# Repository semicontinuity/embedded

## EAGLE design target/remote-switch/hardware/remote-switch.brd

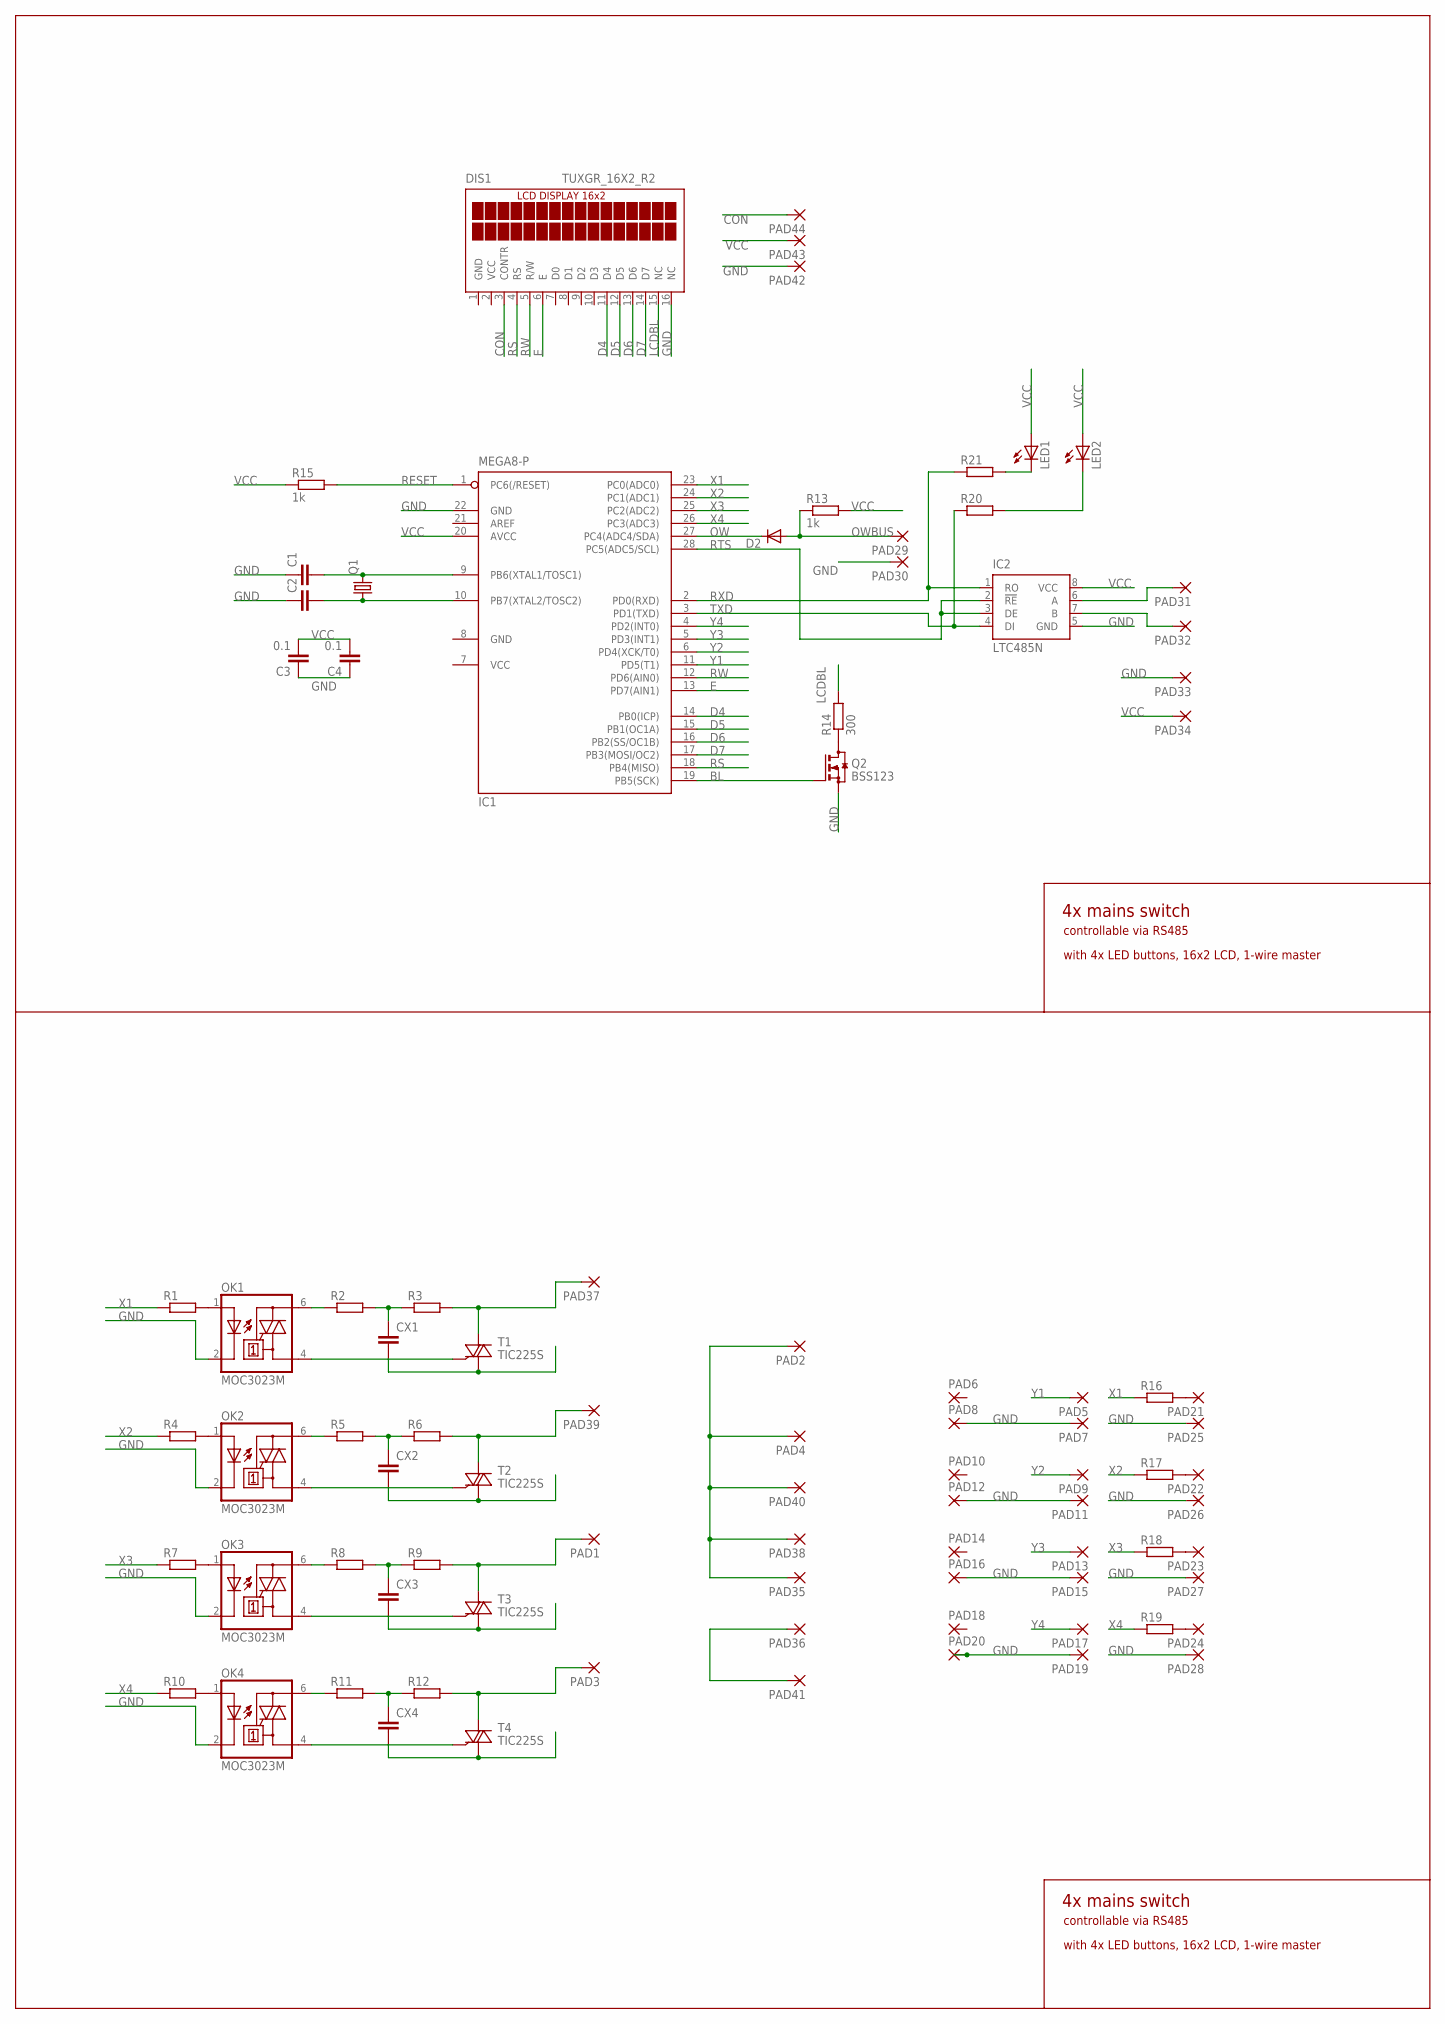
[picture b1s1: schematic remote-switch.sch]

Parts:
C1, C2: C-EUC0805; C0805
C3, C4: 0.1; C0805
CX1, CX2, CX3, CX4: CXXC15B5; XC15B5
D2: DIODE-MINIMELF; MINIMELF
DIS1: TUXGR_16X2_R2
IC1: MEGA8-P; DIL28-3
IC2: LTC485N; DIL08
LED1, LED2: LEDSML0805; SML0805
OK1, OK2, OK3, OK4: MOC3023M; DIL06
PAD1, PAD2, PAD3, PAD4, PAD29, PAD30, PAD31, PAD32, PAD33, PAD34, PAD35, PAD36, PAD37, PAD38, PAD39, PAD40, PAD41: 2,54/0,8
PAD5, PAD6, PAD7, PAD8, PAD9, PAD10, PAD11, PAD12, PAD13, PAD14, PAD15, PAD16, PAD17, PAD18, PAD19, PAD20, PAD21, PAD22, PAD23, PAD24, PAD25, PAD26, PAD27, PAD28, PAD42, PAD43, PAD44: 1,6/0,8
Q1: CRYSTALHC49S; HC49/S
Q2: BSS123; SOT23
R1, R4, R7, R10, R16, R17, R18, R19, R20, R21: R-EU_M0805; M0805
R2, R3, R5, R6, R8, R9, R11, R12: R-EU_R1206; R1206
R13, R15: 1k; R0805
R14: 300; R0805
T1, T2, T3, T4: TIC225S; TO220DS

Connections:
BL: IC1.19 (PB5(SCK)), Q2.1 (G)
CON: DIS1.3 (CONTR), PAD44.1
D4: DIS1.11 (D4), IC1.14 (PB0(ICP))
D5: DIS1.12 (D5), IC1.15 (PB1(OC1A))
D6: DIS1.13 (D6), IC1.16 (PB2(SS/OC1B))
D7: DIS1.14 (D7), IC1.17 (PB3(MOSI/OC2))
E: DIS1.6 (E), IC1.13 (PD7(AIN1))
GND: C1.1, C2.1, C3.1, C4.1, DIS1.1 (GND), DIS1.16 (NC), IC1.8 (GND), IC1.22 (GND), IC2.5 (GND), OK1.2 (C), OK2.2 (C), OK3.2 (C), OK4.2 (C), PAD7.1, PAD8.1, PAD11.1, PAD12.1, PAD15.1, PAD16.1, PAD19.1, PAD20.1, PAD25.1, PAD26.1, PAD27.1, PAD28.1, PAD30.1, PAD33.1, PAD42.1, Q2.2 (S)
LCDBL: DIS1.15 (NC), R14.2
unnamed: OK1.1 (A), R1.2
unnamed: IC2.6 (A), PAD31.1
unnamed: C1.2, IC1.9 (PB6(XTAL1/TOSC1)), Q1.2
unnamed: OK1.6 (A2), R2.1
unnamed: CX1.1, R2.2, R3.1
unnamed: OK1.4 (A1), T1.G
unnamed: PAD37.1, R3.2, T1.A2
unnamed: CX1.2, T1.A1
unnamed: OK2.1 (A), R4.2
unnamed: C2.2, IC1.10 (PB7(XTAL2/TOSC2)), Q1.1
unnamed: Q2.3 (D), R14.1
unnamed: OK2.6 (A2), R5.1
unnamed: OK2.4 (A1), T2.G
unnamed: PAD39.1, R6.2, T2.A2
unnamed: OK3.1 (A), R7.2
unnamed: CX2.1, R5.2, R6.1
unnamed: CX2.2, T2.A1
unnamed: IC2.7 (B), PAD32.1
unnamed: PAD2.1, PAD4.1, PAD35.1, PAD38.1, PAD40.1
unnamed: OK3.6 (A2), R8.1
unnamed: OK3.4 (A1), T3.G
unnamed: PAD1.1, R9.2, T3.A2
unnamed: CX3.1, R8.2, R9.1
unnamed: CX3.2, T3.A1
unnamed: OK4.1 (A), R10.2
unnamed: PAD36.1, PAD41.1
unnamed: PAD21.1, R16.2
unnamed: OK4.6 (A2), R11.1
unnamed: OK4.4 (A1), T4.G
unnamed: PAD3.1, R12.2, T4.A2
unnamed: CX4.1, R11.2, R12.1
unnamed: CX4.2, T4.A1
unnamed: PAD22.1, R17.2
unnamed: PAD23.1, R18.2
unnamed: PAD24.1, R19.2
unnamed: LED1.C, R21.2
unnamed: LED2.C, R20.2
OW: D2.C, IC1.27 (PC4(ADC4/SDA))
OWBUS: D2.A, PAD29.1, R13.1
RESET: IC1.1 (PC6(/RESET)), R15.2
RS: DIS1.4 (RS), IC1.18 (PB4(MISO))
RTS: IC1.28 (PC5(ADC5/SCL)), IC2.2 (!RE), IC2.3 (DE)
RW: DIS1.5 (R/W), IC1.12 (PD6(AIN0))
RXD: IC1.2 (PD0(RXD)), IC2.1 (RO), R21.1
TXD: IC1.3 (PD1(TXD)), IC2.4 (DI), R20.1
VCC: C3.2, C4.2, DIS1.2 (VCC), IC1.7 (VCC), IC1.20 (AVCC), IC2.8 (VCC), LED1.A, LED2.A, PAD34.1, PAD43.1, R13.2, R15.1
X1: IC1.23 (PC0(ADC0)), R1.1, R16.1
X2: IC1.24 (PC1(ADC1)), R4.1, R17.1
X3: IC1.25 (PC2(ADC2)), R7.1, R18.1
X4: IC1.26 (PC3(ADC3)), R10.1, R19.1
Y1: IC1.11 (PD5(T1)), PAD5.1
Y2: IC1.6 (PD4(XCK/T0)), PAD9.1
Y3: IC1.5 (PD3(INT1)), PAD13.1
Y4: IC1.4 (PD2(INT0)), PAD17.1

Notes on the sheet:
4x mains switch
controllable via RS485
with 4x LED buttons, 16x2 LCD, 1-wire master

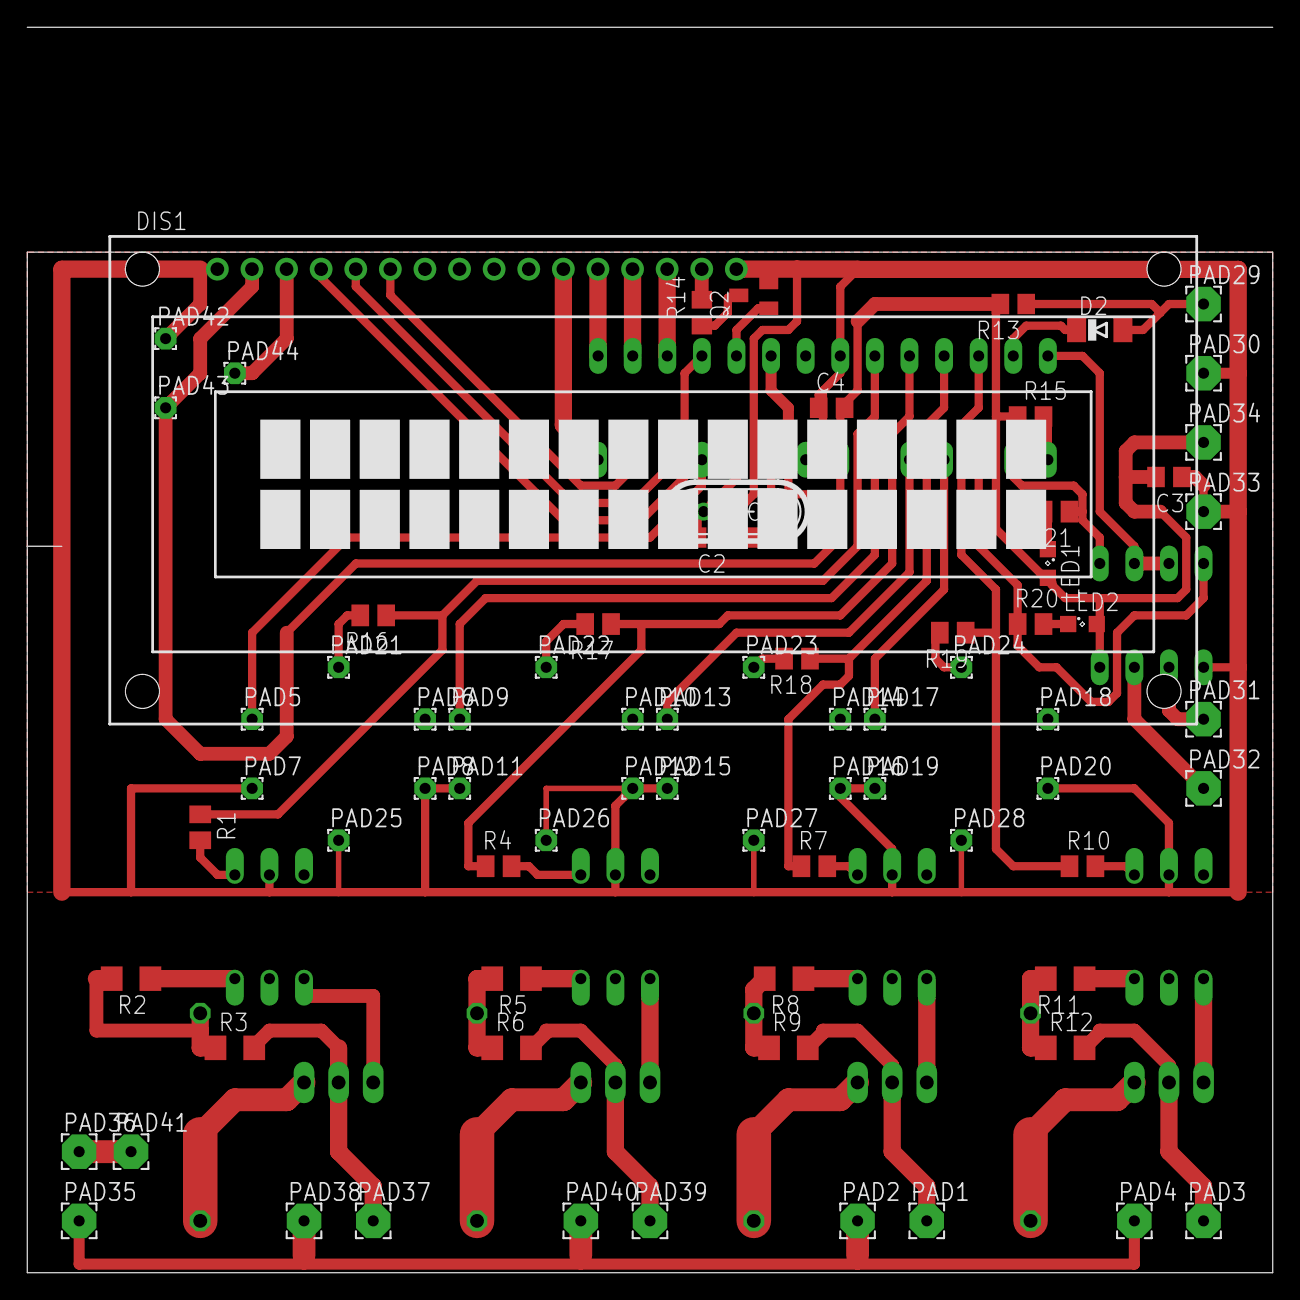
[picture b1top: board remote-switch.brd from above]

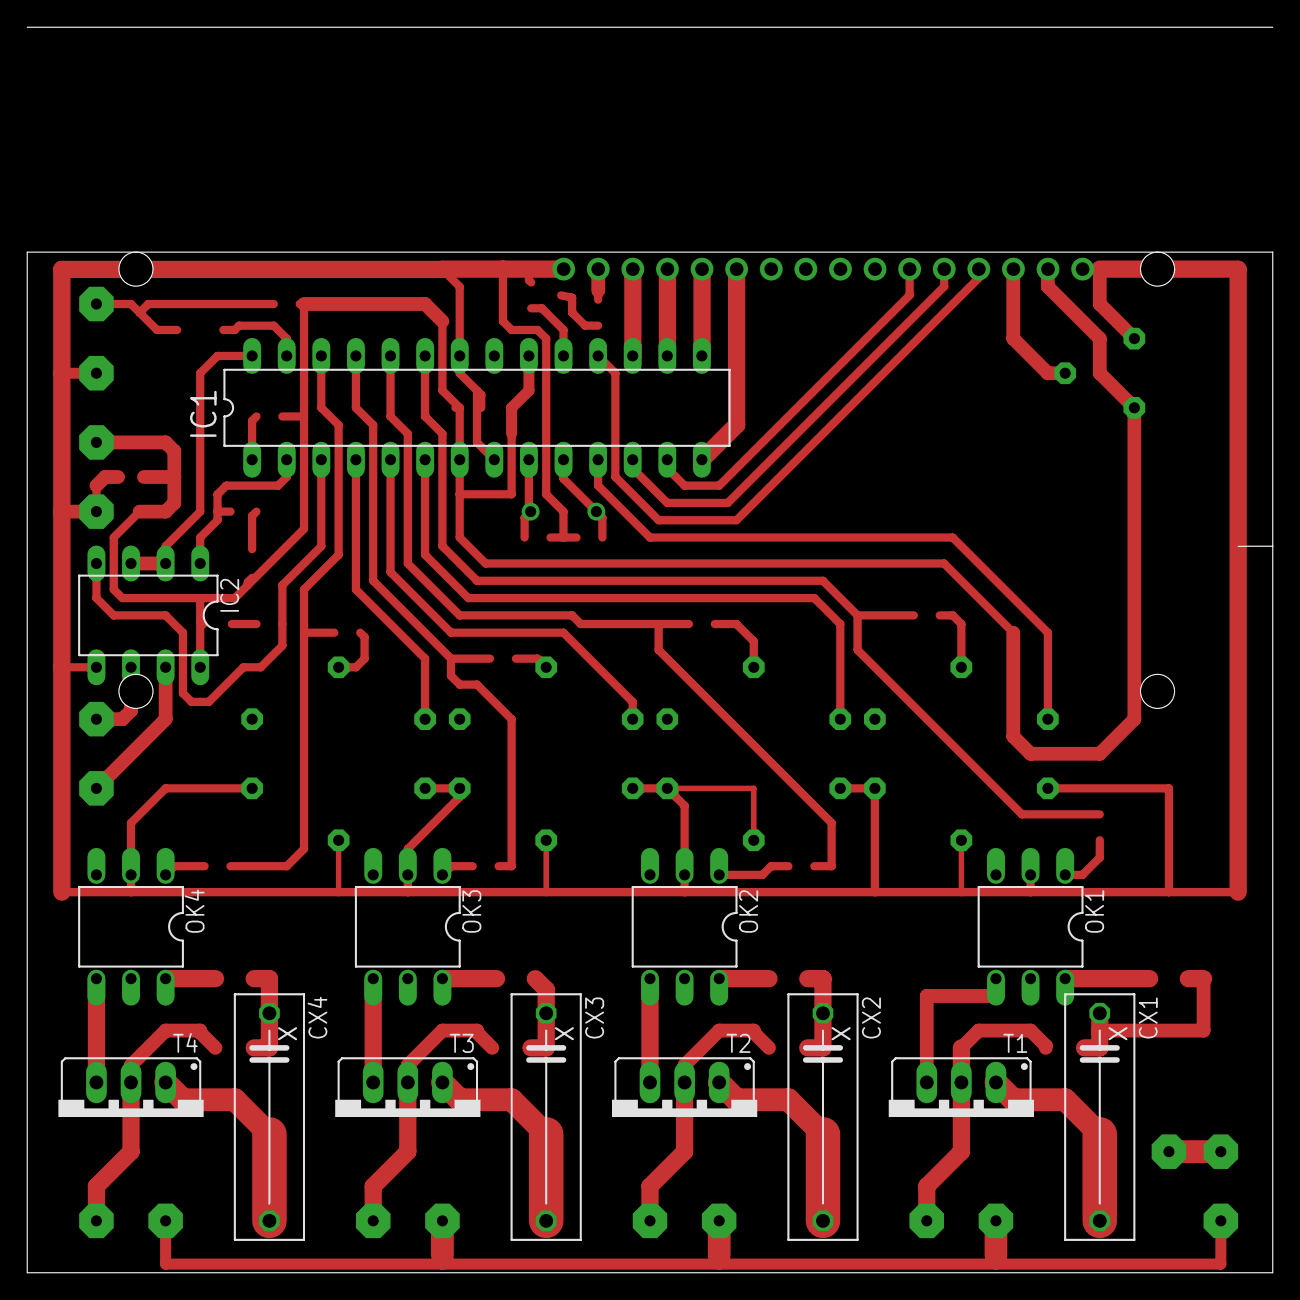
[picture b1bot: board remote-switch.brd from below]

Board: 2 copper layers, 91.4 x 74.9 mm, 89 parts (14 on the bottom side), 63 nets.

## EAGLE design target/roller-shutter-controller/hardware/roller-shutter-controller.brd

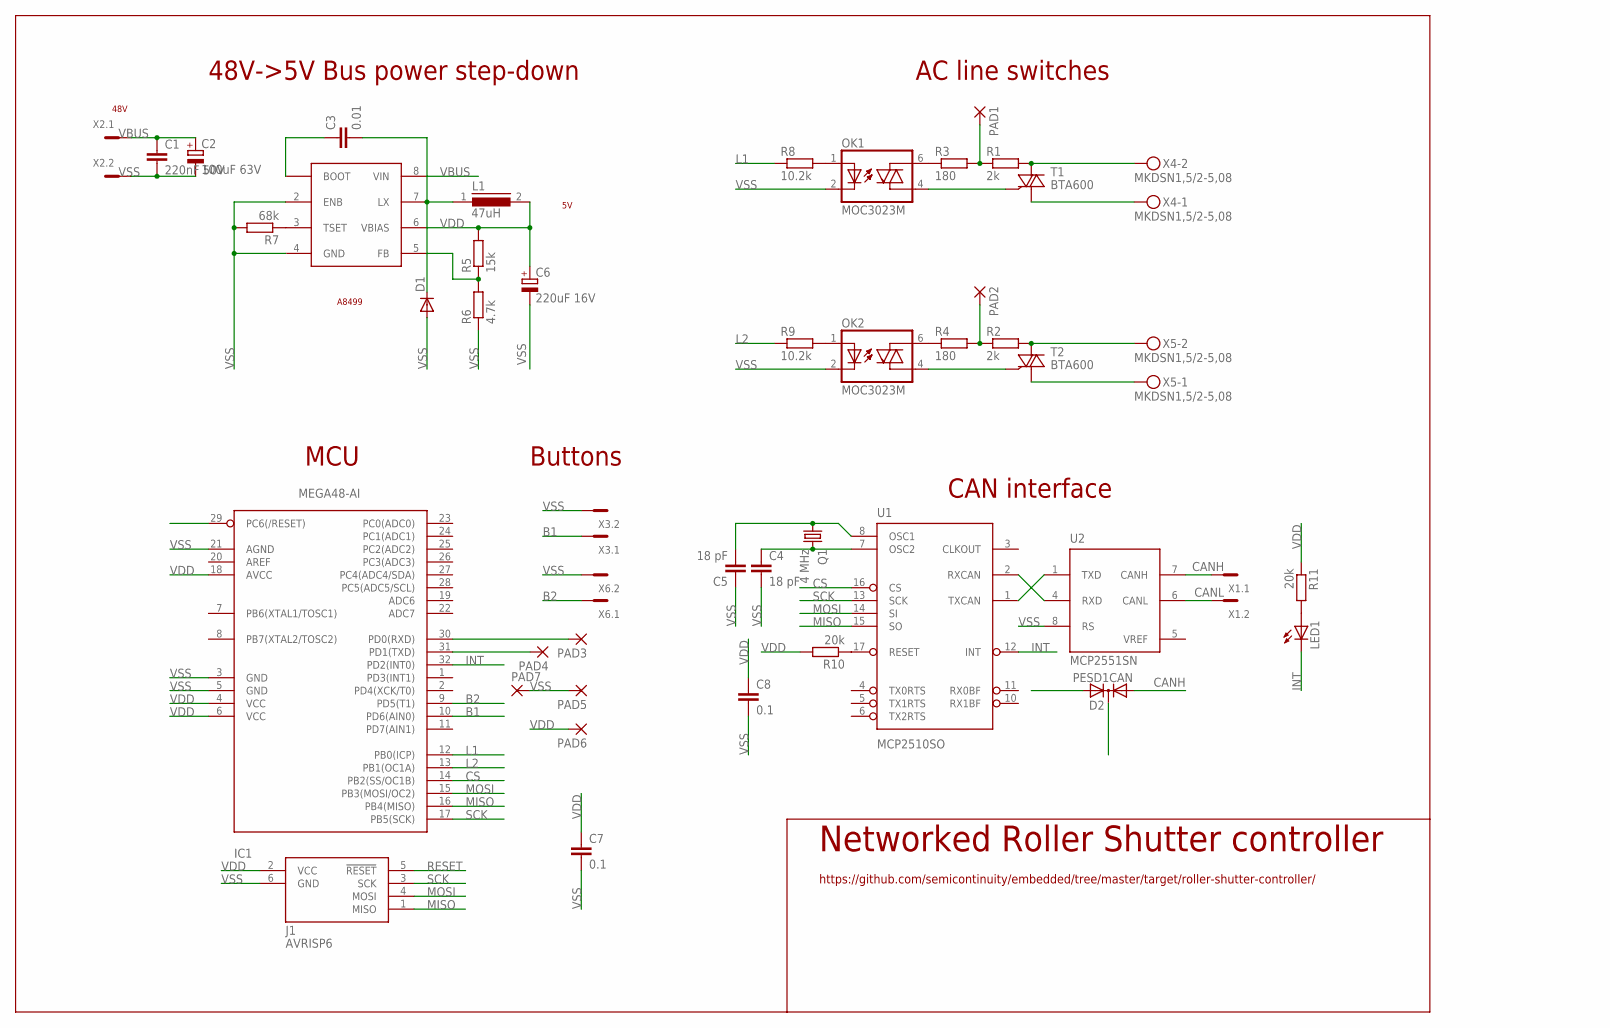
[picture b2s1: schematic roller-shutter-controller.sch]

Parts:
C1: 220nF 50V; C0805
C2: 100uF 63V; 153CLV-1010
C3: 0.01; C0805
C4, C5: 18 pF; C0805
C6: 220uF 16V; 153CLV-0605
C7, C8: 0.1; C0805
D1: DIODE-SMB; SMB
D2: PESD1CAN; SOT323
IC1: MEGA48-AI; TQFP32-08
J1: AVRISP6; CON6P2R
L1: 47uH; DR127
LED1: LEDCHIP-LED0805; CHIP-LED0805
OK1, OK2: MOC3023M; DIL06
PAD1, PAD2, PAD3, PAD4, PAD5, PAD6, PAD7: 1,6/0,8
Q1: 4 MHz; HC49/S
R1, R2: 2k; M0805
R3, R4: 180; M0805
R5: 15k; R0805
R6: 4.7k; R0805
R7: 68k; R0805
R8, R9: 10.2k; R0805
R10, R11: 20k; R0805
T1, T2: BTA600; TO220DS
U1: MCP2510SO; SO-18W
U2: MCP2551SN; SO-08
U$1: A8499; SO08
X1, X2, X3, X6: MCV2
X4, X5: MKDSN1,5/2-5,08

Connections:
B1: IC1.10 (PD6(AIN0)), X3.1
B2: IC1.9 (PD5(T1)), X6.1
BOOT: C3.1, U$1.1 (BOOT)
CANH: D2.1 (A1), U2.7 (CANH), X1.1
CANL: D2.2 (A2), U2.6 (CANL), X1.2
CS: IC1.14 (PB2(SS/OC1B)), U1.16 (CS)
INT: IC1.32 (PD2(INT0)), LED1.C, U1.12 (INT)
L1: IC1.12 (PB0(ICP)), R8.1
L2: IC1.13 (PB1(OC1A)), R9.1
LX: C3.2, D1.C, L1.1, U$1.7 (LX)
MISO: IC1.16 (PB4(MISO)), J1.1 (MISO), U1.15 (SO)
MOSI: IC1.15 (PB3(MOSI/OC2)), J1.4 (MOSI), U1.14 (SI)
unnamed: R1.2, T1.A2, X4.2
unnamed: T1.A1, X4.1
unnamed: R2.2, T2.A2, X5.2
unnamed: OK1.6 (A2), R3.1
unnamed: PAD1.1, R1.1, R3.2
unnamed: OK1.4 (A1), T1.G
unnamed: OK2.6 (A2), R4.1
unnamed: OK2.4 (A1), T2.G
unnamed: PAD2.1, R2.1, R4.2
unnamed: T2.A1, X5.1
unnamed: C4.1, Q1.2, U1.7 (OSC2)
unnamed: C5.2, Q1.1, U1.8 (OSC1)
unnamed: IC1.30 (PD0(RXD)), PAD3.1
unnamed: R5.1, R6.2, U$1.5 (FB)
unnamed: R7.1, U$1.3 (TSET)
unnamed: IC1.31 (PD1(TXD)), PAD4.1
unnamed: OK1.1 (A), R8.2
unnamed: OK2.1 (A), R9.2
unnamed: R10.1, U1.17 (RESET)
unnamed: LED1.A, R11.2
RESET: IC1.29 (PC6(/RESET)), J1.5 (!RESET)
RXD: U1.2 (RXCAN), U2.4 (RXD)
SCK: IC1.17 (PB5(SCK)), J1.3 (SCK), U1.13 (SCK)
TXD: U1.1 (TXCAN), U2.1 (TXD)
VBUS: C1.1, C2.+, U$1.8 (VIN), X2.1
VDD: C6.+, C7.1, C8.1, IC1.4 (VCC), IC1.6 (VCC), IC1.18 (AVCC), J1.2 (VCC), L1.2, PAD6.1, R5.2, R10.2, R11.1, U1.18 (VDD), U2.3 (VDD), U$1.6 (VBIAS)
VREF: U2.5 (VREF)
VSS: C1.2, C2.-, C4.2, C5.1, C6.-, C7.2, C8.2, D1.A, D2.3 (C), IC1.3 (GND), IC1.5 (GND), IC1.21 (AGND), J1.6 (GND), OK1.2 (C), OK2.2 (C), PAD5.1, PAD7.1, R6.1, R7.2, U1.9 (VSS), U2.2 (VSS), U2.8 (RS), U$1.2 (ENB), U$1.4 (GND), X2.2, X3.2, X6.2

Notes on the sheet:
Networked Roller Shutter controller
https://github.com/semicontinuity/embedded/tree/master/target/roller-shutter-controller/
CAN interface
AC line switches
48V->5V Bus power step-down
MCU
Buttons
A8499
48V

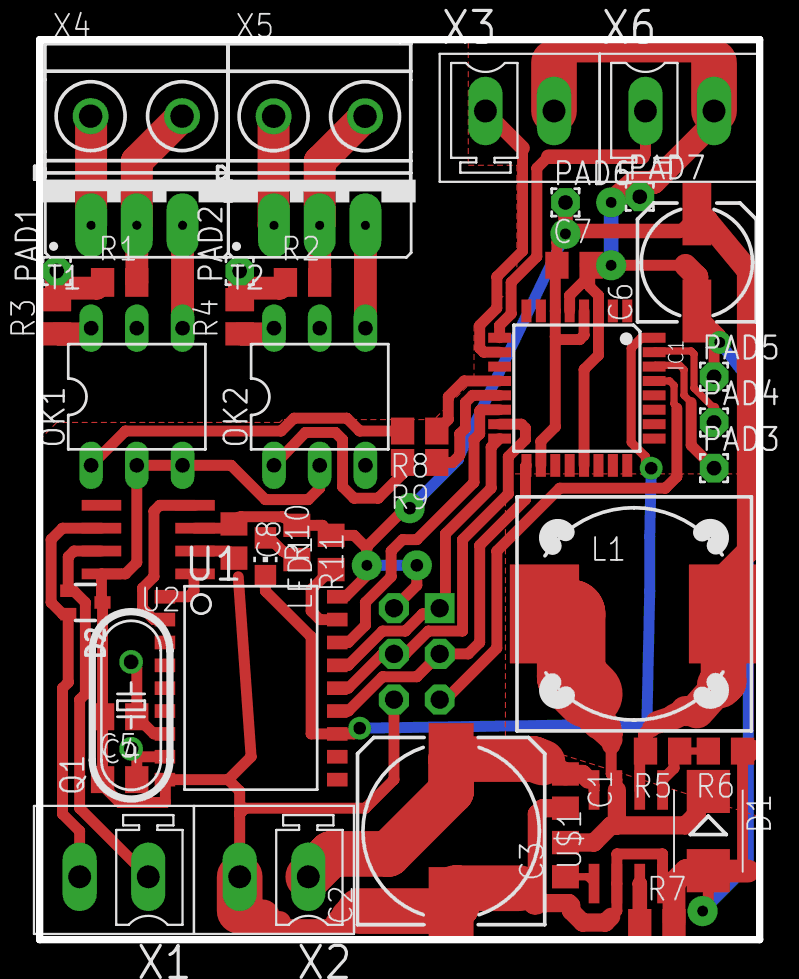
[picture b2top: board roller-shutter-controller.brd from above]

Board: 2 copper layers, 40.0 x 50.0 mm, 46 parts (1 on the bottom side), 39 nets.

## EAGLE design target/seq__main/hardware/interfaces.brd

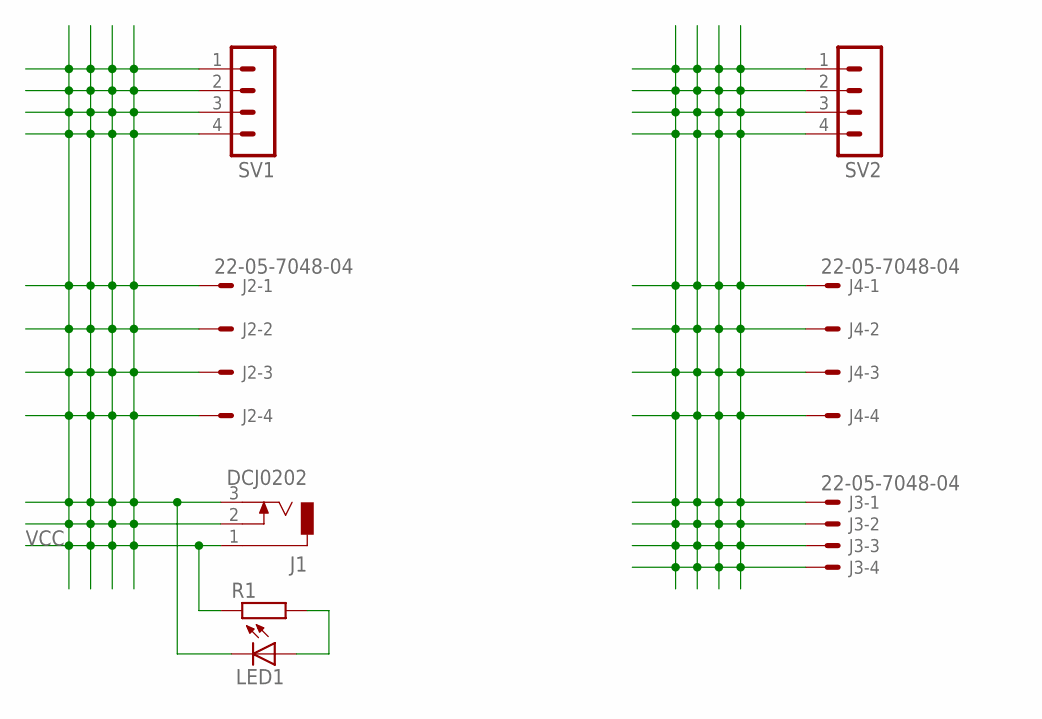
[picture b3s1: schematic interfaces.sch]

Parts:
J1: DCJ0202
J2, J3, J4: 22-05-7048-04; 7395-04
LED1: LEDSML0805; SML0805
R1: R-EU_R0805; R0805
SV1, SV2: MA04-1

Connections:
unnamed: LED1.A, R1.2
unnamed: J3.1, J3.2, J3.3, J3.4, J4.1, J4.2, J4.3, J4.4, SV2.1, SV2.2, SV2.3, SV2.4
VCC: J1.1, J1.2, J1.3, J2.1, J2.2, J2.3, J2.4, LED1.C, R1.1, SV1.1, SV1.2, SV1.3, SV1.4

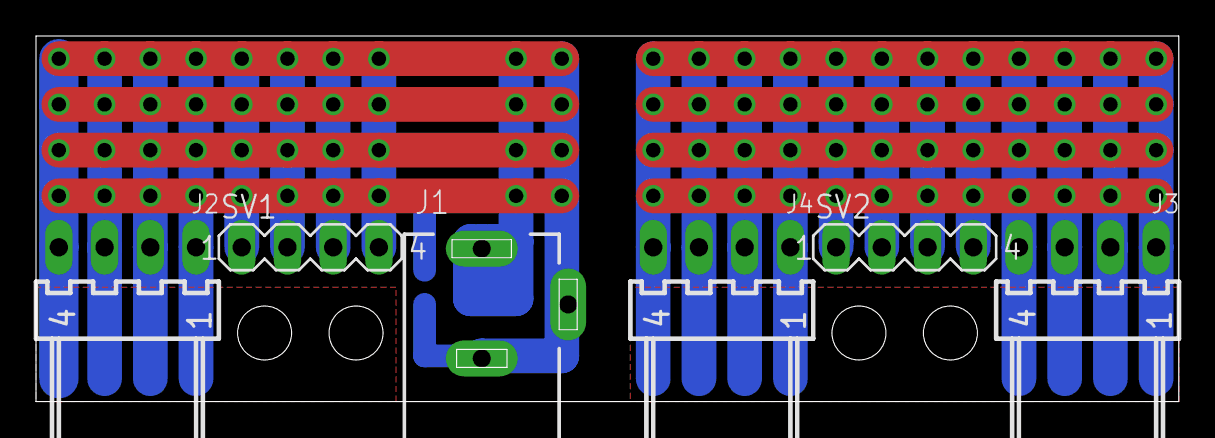
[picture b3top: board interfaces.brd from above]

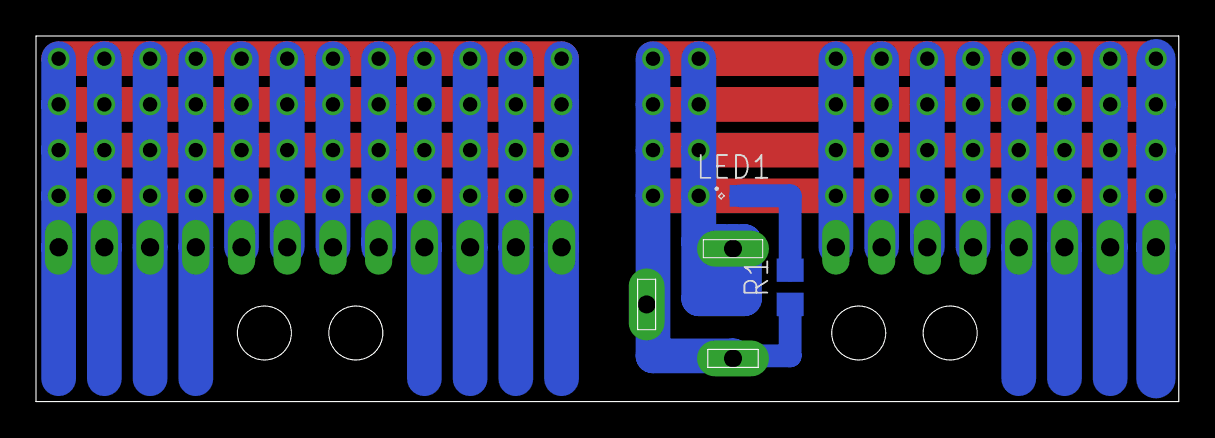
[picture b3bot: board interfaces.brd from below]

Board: 2 copper layers, 63.5 x 20.3 mm, 8 parts (2 on the bottom side), 3 nets.
